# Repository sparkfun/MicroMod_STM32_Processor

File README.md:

SparkFun STM32 MicroMod Processor
========================================

[*SparkFun STM32 MicroMod Processor v20 (21326)*](https://www.sparkfun.com/products/21326)

We've brought the power and precision of the STM32 Processor to the [SparkFun MicroMod ecosystem](https://www.sparkfun.com/micromod)! Please welcome the [MicroMod STM32 Processor Board](https://www.sparkfun.com/products/21326)! With the high-performance Arm® Cortex®-M4 32-bit RISC core, Flash memory up to 1 Mbyte, up to 192 Kbytes of SRAM, a memory protection unit (MPU), high-speed embedded memories, up to 4 Kbytes of backup SRAM, and an extensive range of enhanced I/Os and peripherals, this board is chock full of functionality. 

Repository Contents
-------------------

* **/Hardware** - Eagle design files (.brd, .sch)
* **/Production** - Production panel files (.brd)

Documentation
--------------
* **[Hookup Guide](https://learn.sparkfun.com/tutorials/micromod-stm32-processor-hookup-guide)** - Basic hookup guide for the MicroMod STM32 Processor Board.
* **[Getting Started with MicroMod](https://learn.sparkfun.com/tutorials/getting-started-with-micromod)** - A tutorial to help you get started with the MicroMod Ecosystem. 
* **[Designing with MicroMod](https://learn.sparkfun.com/tutorials/designing-with-micromod)** - A tutorial to walk you through the specs of the MicroMod processor and carrier board as well as the basics of incorporating the MicroMod form factor into your own PCB designs.

License Information
-------------------

This product is _**open source**_! 

Please review the LICENSE.md file for license information. 

If you have any questions or concerns on licensing, please contact technical support on our [SparkFun forums](https://forum.sparkfun.com/viewforum.php?f=152).

Distributed as-is; no warranty is given.

- Your friends at SparkFun.

_<COLLABORATION CREDIT>_

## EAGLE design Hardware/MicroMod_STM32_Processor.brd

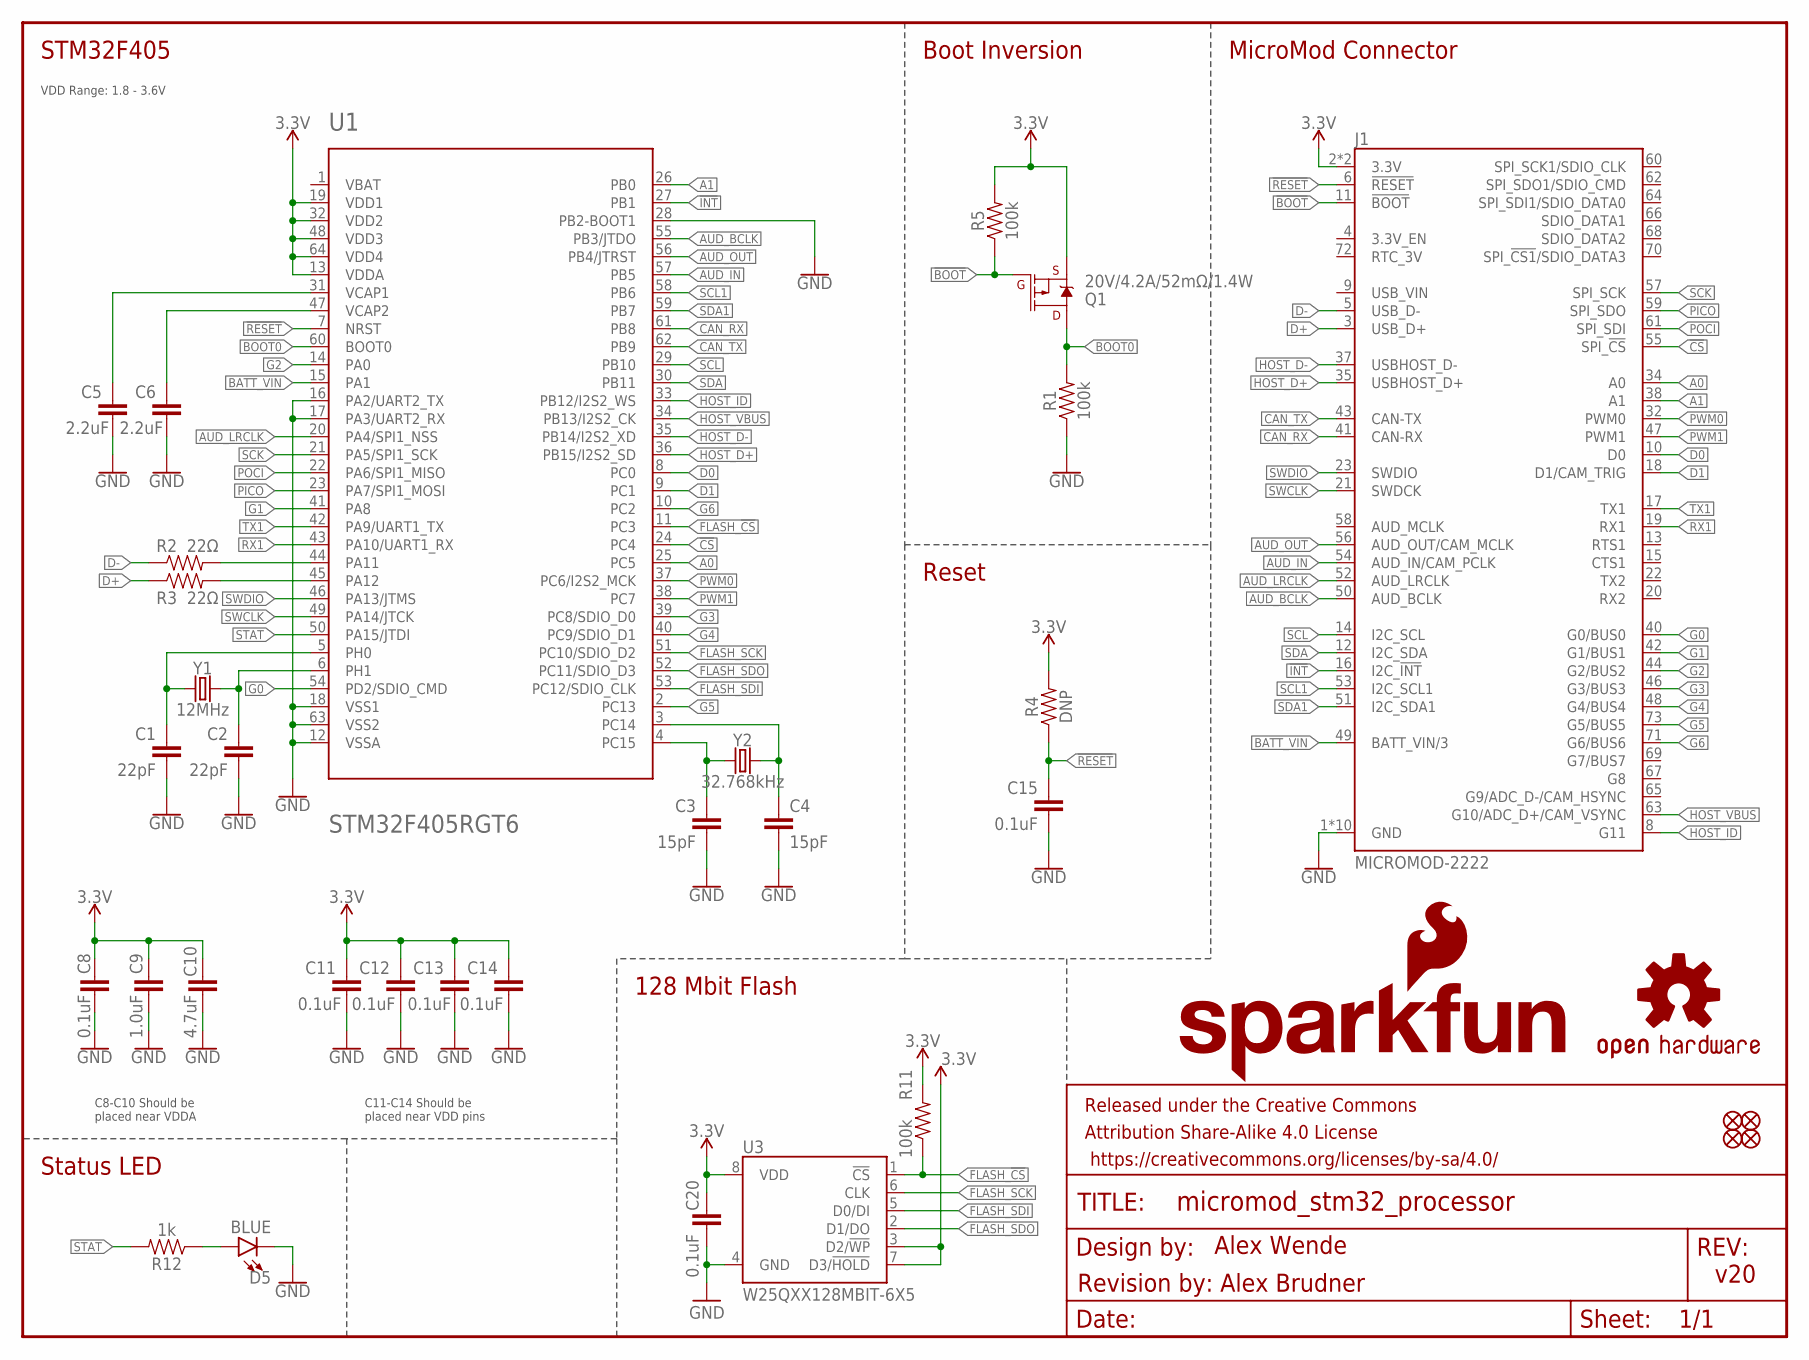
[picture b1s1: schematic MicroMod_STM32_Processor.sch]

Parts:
C1, C2: 22pF; 0402-TIGHT
C3, C4: 15pF; 0402-TIGHT
C5, C6: 2.2uF; 0402-TIGHT
C8, C11, C12, C13, C14, C15, C20: 0.1uF; 0402-TIGHT
C9: 1.0uF; 0402-TIGHT
C10: 4.7uF; 0402-TIGHT
D5: BLUE; LED-0603
FD1, FD2, FD3, FD4: FIDUCIALUFIDUCIAL; FIDUCIAL-MICRO
FRAME1: FRAME-LETTER; CREATIVE_COMMONS
J1: MICROMOD-2222; M.2-CARD-E-22
LOGO2: OSHW-LOGOS; OSHW-LOGO-S
LOGO3: SFE_LOGO_NAME_FLAME.1_INCH; SFE_LOGO_NAME_FLAME_.1
Q1: 20V/4.2A/52mΩ/1.4W; SOT23-3
R1, R5, R11: 100k; 0402-TIGHT
R2, R3: 22Ω; 0402-TIGHT
R4: DNP; 0402-TIGHT_NO_CREAM
R12: 1k; 0402-TIGHT
U1: STM32F405RGT6; TQFP64
U3: W25QXX128MBIT-6X5; WSON-8-6X5
Y1: 12MHz; CRYSTAL-SMD-5X3.2-4PAD
Y2: 32.768kHz; CRYSTAL-SMD-3.2X1.5MM

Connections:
3.3V: C8.1, C9.1, C10.1, C11.1, C12.1, C13.1, C14.1, C20.1, J1.2 (3.3V), J1.74 (3.3V), Q1.2 (S), R4.2, R5.2, R11.2, U1.13 (VDDA), U1.19 (VDD1), U1.32 (VDD2), U1.48 (VDD3), U1.64 (VDD4), U3.3 (D2/!WP!), U3.7 (D3/!HOLD!), U3.8 (VDD)
!BOOT: J1.11 (!BOOT!), Q1.1 (G), R5.1
!CS: J1.55 (SPI_!CS!), U1.24 (PC4)
!INT: J1.16 (I2C_!INT!), U1.27 (PB1)
!RESET: C15.1, J1.6 (!RESET!), R4.1, U1.7 (NRST)
A0: J1.34 (A0), U1.25 (PC5)
A1: J1.38 (A1), U1.26 (PB0)
AUD_BCLK: J1.50 (AUD_BCLK), U1.55 (PB3/JTDO)
AUD_IN: J1.54 (AUD_IN/CAM_PCLK), U1.57 (PB5)
AUD_LRCLK: J1.52 (AUD_LRCLK), U1.20 (PA4/SPI1_NSS)
AUD_OUT: J1.56 (AUD_OUT/CAM_MCLK), U1.56 (PB4/JTRST)
BATT_VIN: J1.49 (BATT_VIN/3), U1.15 (PA1)
BOOT0: Q1.3 (D), R1.2, U1.60 (BOOT0)
CAN_RX: J1.41 (CAN-RX), U1.61 (PB8)
CAN_TX: J1.43 (CAN-TX), U1.62 (PB9)
D0: J1.10 (D0), U1.8 (PC0)
D1: J1.18 (D1/CAM_TRIG), U1.9 (PC1)
D+: J1.3 (USB_D+), R3.1
D-: J1.5 (USB_D-), R2.1
FLASH_!CS: R11.1, U1.11 (PC3), U3.1 (!CS!)
FLASH_SCK: U1.51 (PC10/SDIO_D2), U3.6 (CLK)
FLASH_SDI: U1.53 (PC12/SDIO_CLK), U3.5 (D0/DI)
FLASH_SDO: U1.52 (PC11/SDIO_D3), U3.2 (D1/DO)
G0: J1.40 (G0/BUS0), U1.54 (PD2/SDIO_CMD)
G1: J1.42 (G1/BUS1), U1.41 (PA8)
G2: J1.44 (G2/BUS2), U1.14 (PA0)
G3: J1.46 (G3/BUS3), U1.39 (PC8/SDIO_D0)
G4: J1.48 (G4/BUS4), U1.40 (PC9/SDIO_D1)
G5: J1.73 (G5/BUS5), U1.2 (PC13)
G6: J1.71 (G6/BUS6), U1.10 (PC2)
GND: C1.2, C2.2, C3.2, C4.2, C5.2, C6.2, C8.2, C9.2, C10.2, C11.2, C12.2, C13.2, C14.2, C15.2, C20.2, D5.C, J1.1 (GND), J1.7 (GND), J1.33 (GND), J1.36 (GND), J1.39 (GND), J1.45 (GND), J1.75 (GND), J1.GND1 (GND), J1.GND2 (GND), J1.GND3 (GND), R1.1, U1.12 (VSSA), U1.16 (PA2/UART2_TX), U1.17 (PA3/UART2_RX), U1.18 (VSS1), U1.28 (PB2-BOOT1), U1.63 (VSS2), U3.4 (GND)
HOST_D+: J1.35 (USBHOST_D+), U1.36 (PB15/I2S2_SD)
HOST_D-: J1.37 (USBHOST_D-), U1.35 (PB14/I2S2_XD)
HOST_ID: J1.8 (G11), U1.33 (PB12/I2S2_WS)
HOST_VBUS: J1.63 (G10/ADC_D+/CAM_VSYNC), U1.34 (PB13/I2S2_CK)
unnamed: D5.A, R12.1
unnamed: R2.2, U1.44 (PA11)
unnamed: R3.2, U1.45 (PA12)
unnamed: C4.1, U1.3 (PC14), Y2.P$2 (2)
unnamed: C3.1, U1.4 (PC15), Y2.P$1 (1)
unnamed: C2.1, U1.6 (PH1), Y1.3 (2)
unnamed: C1.1, U1.5 (PH0), Y1.1
unnamed: C6.1, U1.47 (VCAP2)
unnamed: C5.1, U1.31 (VCAP1)
PICO: J1.59 (SPI_SDO), U1.23 (PA7/SPI1_MOSI)
POCI: J1.61 (SPI_SDI), U1.22 (PA6/SPI1_MISO)
PWM0: J1.32 (PWM0), U1.37 (PC6/I2S2_MCK)
PWM1: J1.47 (PWM1), U1.38 (PC7)
RX1: J1.19 (RX1), U1.43 (PA10/UART1_RX)
SCK: J1.57 (SPI_SCK), U1.21 (PA5/SPI1_SCK)
SCL: J1.14 (I2C_SCL), U1.29 (PB10)
SCL1: J1.53 (I2C_SCL1), U1.58 (PB6)
SDA: J1.12 (I2C_SDA), U1.30 (PB11)
SDA1: J1.51 (I2C_SDA1), U1.59 (PB7)
STAT: R12.2, U1.50 (PA15/JTDI)
SWCLK: J1.21 (SWDCK), U1.49 (PA14/JTCK)
SWDIO: J1.23 (SWDIO), U1.46 (PA13/JTMS)
TX1: J1.17 (TX1), U1.42 (PA9/UART1_TX)

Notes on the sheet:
128 Mbit Flash
Status LED
C11-C14 Should be placed near VDD pins
C8-C10 Should be placed near VDDA
Boot Inversion
Reset
MicroMod Connector
STM32F405
v20
Alex Wende
VDD Range: 1.8 - 3.6V
Revision by: Alex Brudner

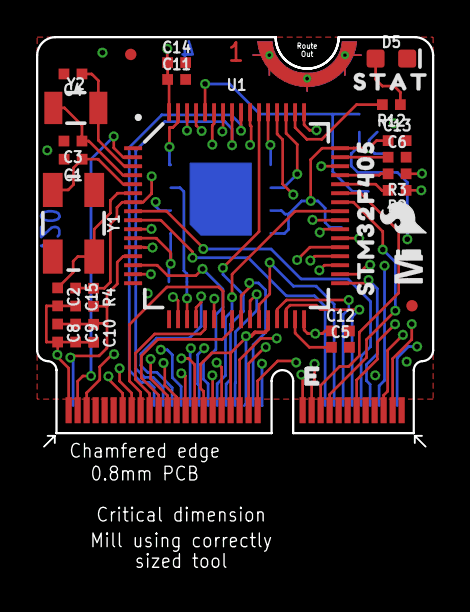
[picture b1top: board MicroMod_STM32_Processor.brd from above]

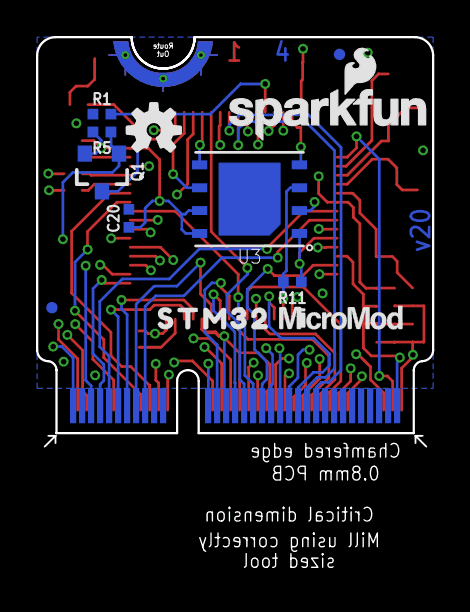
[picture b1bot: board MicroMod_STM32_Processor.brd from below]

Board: 4 copper layers, 22.0 x 22.8 mm, 43 parts (12 on the bottom side), 58 nets.

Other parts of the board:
U$1: STAT0
U$2: STM320
U$3: MICROMOD_MI_LOGO_.35
U$4: STM32F4050
U$5: MICROMOD_LOGO_.3
U$6: SFE_LOGO_FLAME_.1
U$7: PRODUCTION_INSTRUCTIONS

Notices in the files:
parts and their libraries:
SparkFun-Capacitors: Licensing: Creative Commons ShareAlike 4.0 International - https://creativecommons.org/licenses/by-sa/4.0
SparkFun-Aesthetics: Released under the Creative Commons Attribution Share-Alike 4.0 License
SparkFun-Aesthetics: https://creativecommons.org/licenses/by-sa/4.0
